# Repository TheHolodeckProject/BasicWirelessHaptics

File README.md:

BasicWirelessHaptics
====================

Simple Unity project to connect to and actuate the Wireless Haptics device

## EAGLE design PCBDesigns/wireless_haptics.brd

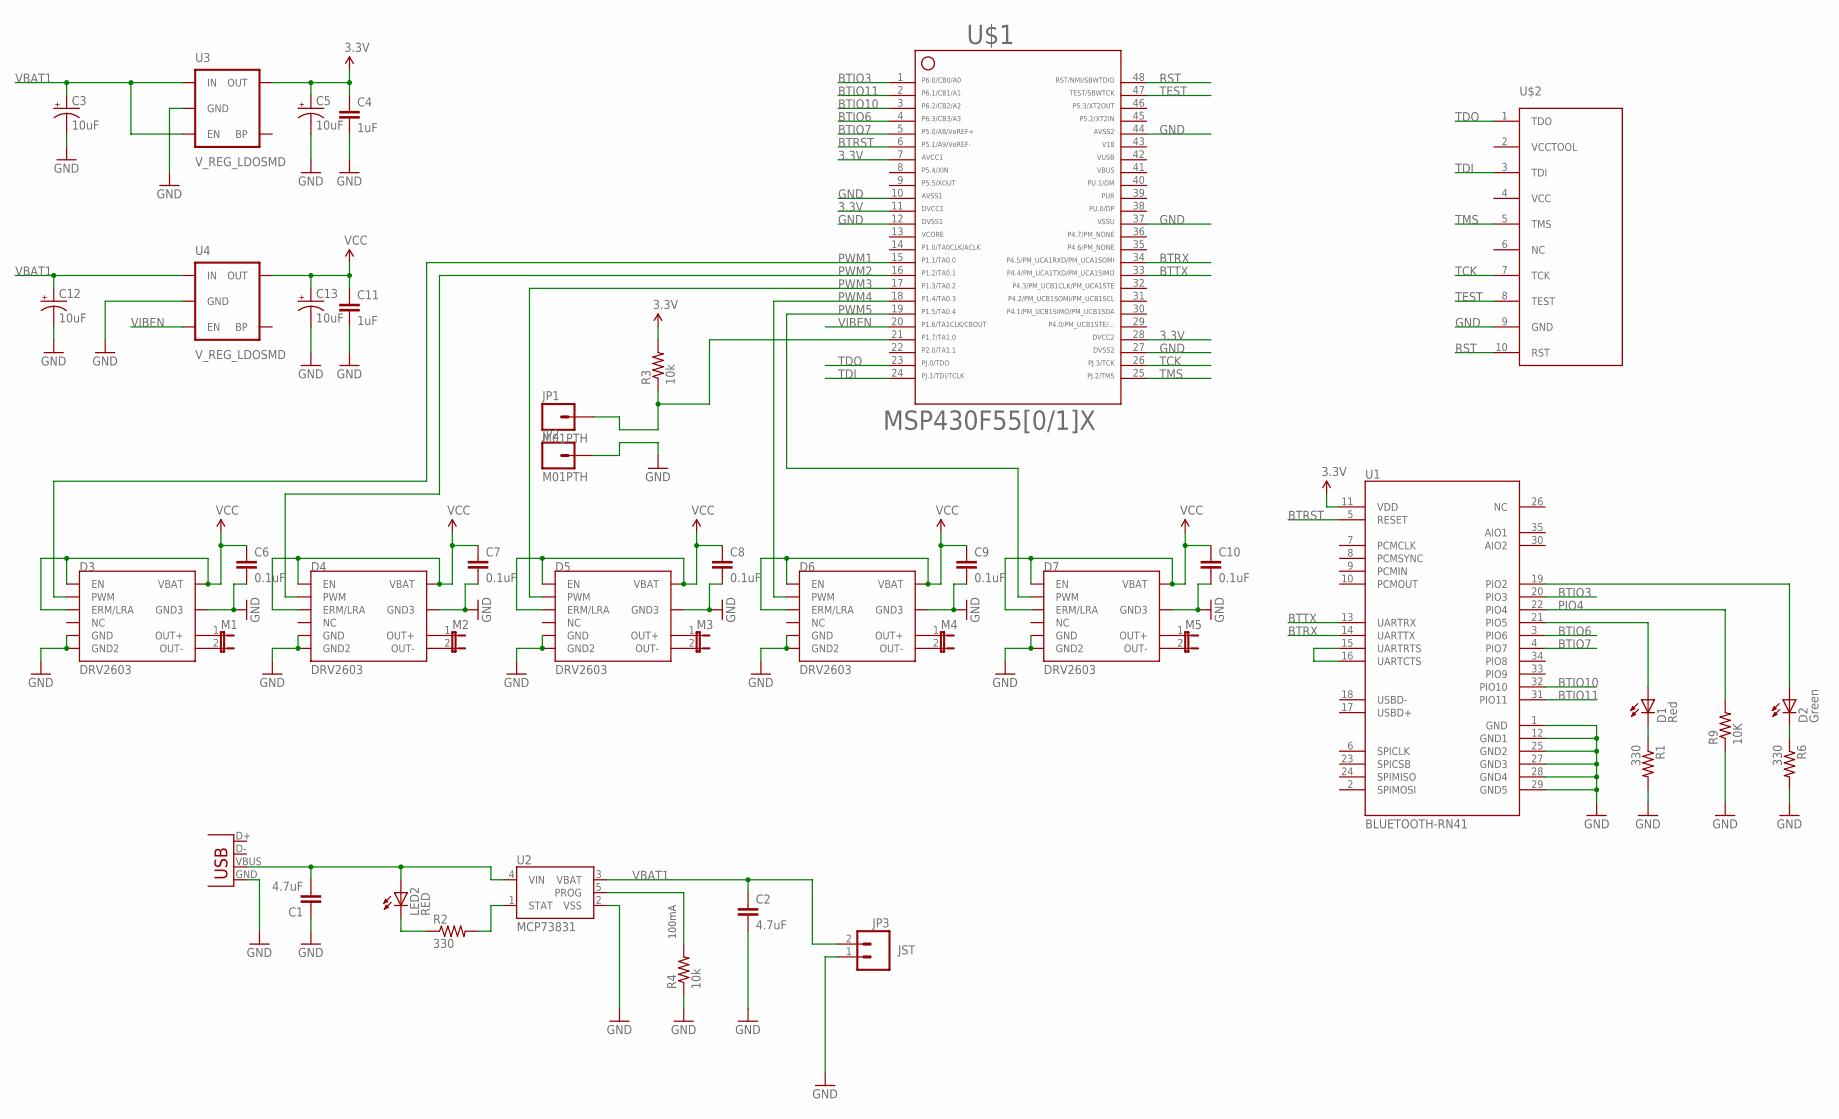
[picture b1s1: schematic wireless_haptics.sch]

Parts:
C1, C2: 4.7uF; 0402-CAP
C3, C5, C12, C13: 10uF; EIA3216
C4, C11: 1uF; 0402-CAP
C6, C7, C8, C9, C10: 0.1uF; 0805
D1: Red; LED-0603
D2: Green; LED-0603
D3, D4, D5, D6, D7: DRV2603; QFN
JP1, JP2: M01PTH; 1X01
JP3: JST; JST-2-PTH
LED2: RED; LED-0603
M1, M2, M3, M4, M5: JUMPER-2PTH; 1X02
R1, R2, R6: 330; 0402-RES
R3, R4: 10k; 0402-RES
R9: 10K; 0402-RES
U1: BLUETOOTH-RN41; RN41
U2: MCP73831; SOT23-5
U3, U4: V_REG_LDOSMD; SOT23-5
U$1: F55[0/1]X---PT48; PT48
U$2: TC2050-NL-MCP-NL; TC2030-MCP-NL
X1: USBSMD; USB-MINIB

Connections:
3.3V: C4.1, C5.A (+), U1.11 (VDD), U3.5 (OUT), U$1.7, U$1.11, U$1.28
13: U$1.13
41: U$1.41
42: U$1.42
43: U$1.43
46: U$1.46
BTIO3: U1.20 (PIO3), U$1.1
BTIO6: U1.3 (PIO6), U$1.4
BTIO7: U1.4 (PIO7), U$1.5
BTIO10: U1.32 (PIO10), U$1.3
BTIO11: U1.31 (PIO11), U$1.2
BTRST: U1.5 (RESET), U$1.6
BTRX: U1.14 (UARTTX), U$1.34
BTTX: U1.13 (UARTRX), U$1.33
D1: D1.C, R1.1
D2: D2.C, R6.1
GND: C1.1, C2.2, C3.C (-), C4.2, C5.C (-), C6.2, C7.2, C8.2, C9.2, C10.2, C11.2, C12.C (-), C13.C (-), D3.P$5 (GND), D3.P$8 (GND2), D3.P$10 (GND3), D4.P$5 (GND), D4.P$8 (GND2), D4.P$10 (GND3), D5.P$5 (GND), D5.P$8 (GND2), D5.P$10 (GND3), D6.P$5 (GND), D6.P$8 (GND2), D6.P$10 (GND3), D7.P$5 (GND), D7.P$8 (GND2), D7.P$10 (GND3), JP2.1, JP3.1, R1.2, R4.1, R6.2, R9.1, U1.1 (GND), U1.12 (GND1), U1.25 (GND2), U1.27 (GND3), U1.28 (GND4), U1.29 (GND5), U2.2 (VSS), U3.2 (GND), U4.2 (GND), U$1.10, U$1.12, U$1.27, U$1.37, U$1.44, U$2.9 (GND), X1.GND
unnamed: D1.A, U1.21 (PIO5)
unnamed: D2.A, U1.19 (PIO2)
unnamed: C1.2, LED2.A, U2.4 (VIN), X1.VBUS
unnamed: D6.P$6 (OUT+), M4.1
unnamed: R2.2, U2.1 (STAT)
unnamed: LED2.C, R2.1
unnamed: D6.P$9 (OUT-), M4.2
unnamed: D7.P$6 (OUT+), M5.1
unnamed: D7.P$9 (OUT-), M5.2
unnamed: D5.P$6 (OUT+), M3.1
unnamed: D5.P$9 (OUT-), M3.2
unnamed: D4.P$6 (OUT+), M2.1
unnamed: D4.P$9 (OUT-), M2.2
unnamed: D3.P$6 (OUT+), M1.1
unnamed: D3.P$9 (OUT-), M1.2
unnamed: U1.15 (UARTRTS), U1.16 (UARTCTS)
unnamed: JP1.1, R3.1, U$1.21
PIO4: R9.2, U1.22 (PIO4)
PROG: R4.2, U2.5 (PROG)
PWM1: D3.P$2 (PWM), U$1.15
PWM2: D4.P$2 (PWM), U$1.16
PWM3: D5.P$2 (PWM), U$1.17
PWM4: D6.P$2 (PWM), U$1.18
PWM5: D7.P$2 (PWM), U$1.19
RST: U$1.48, U$2.10 (RST)
TCK: U$1.26, U$2.7 (TCK)
TDI: U$1.24, U$2.3 (TDI)
TDO: U$1.23, U$2.1 (TDO)
TEST: U$1.47, U$2.8 (TEST)
TMS: U$1.25, U$2.5 (TMS)
VBAT1: C2.1, C3.A (+), C12.A (+), JP3.2, U2.3 (VBAT), U3.1 (IN), U3.3 (EN), U4.1 (IN)
VCC: C6.1, C7.1, C8.1, C9.1, C10.1, C11.1, C13.A (+), D3.P$1 (EN), D3.P$3 (ERM/LRA), D3.P$7 (VBAT), D4.P$1 (EN), D4.P$3 (ERM/LRA), D4.P$7 (VBAT), D5.P$1 (EN), D5.P$3 (ERM/LRA), D5.P$7 (VBAT), D6.P$1 (EN), D6.P$3 (ERM/LRA), D6.P$7 (VBAT), D7.P$1 (EN), D7.P$3 (ERM/LRA), D7.P$7 (VBAT), R3.2, U4.5 (OUT)
VIBEN: U4.3 (EN), U$1.20

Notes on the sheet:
100mA

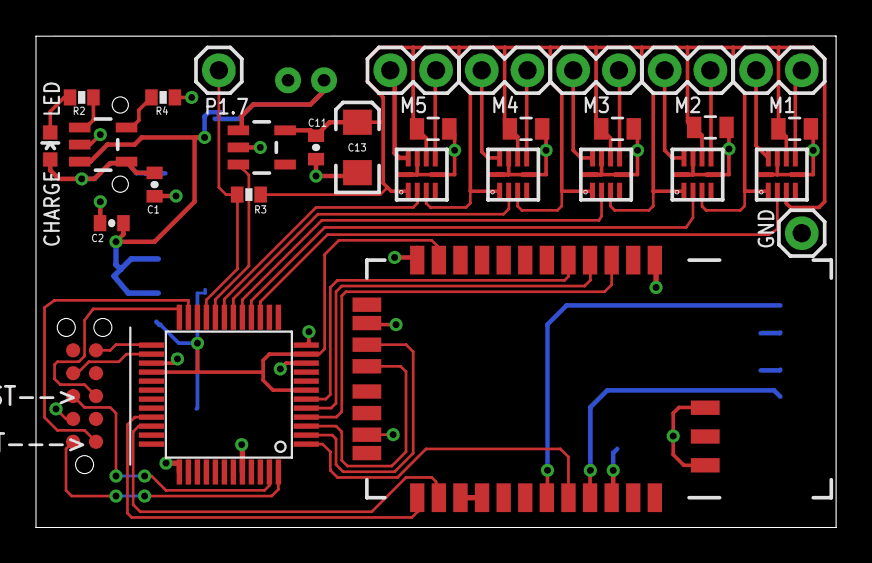
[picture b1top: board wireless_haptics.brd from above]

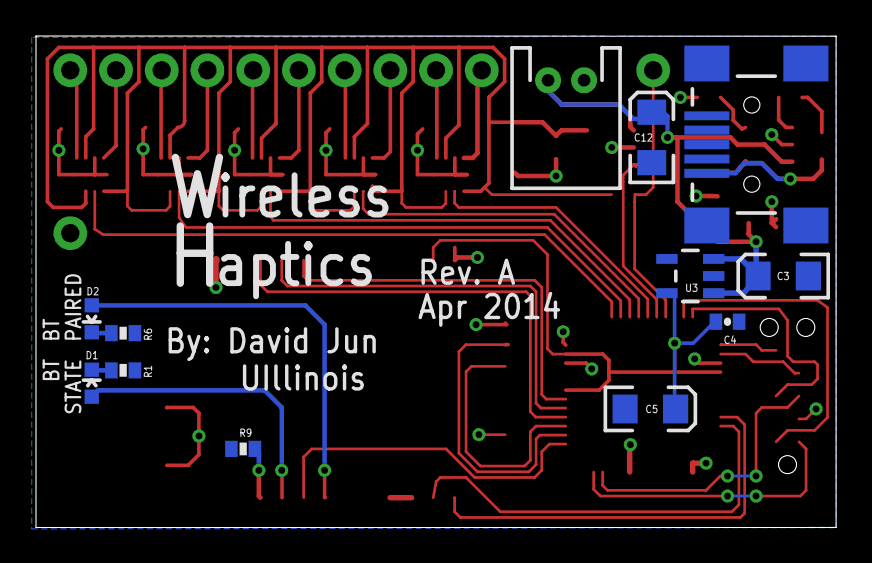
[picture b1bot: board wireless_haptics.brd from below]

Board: 2 copper layers, 44.5 x 27.3 mm, 42 parts (12 on the bottom side), 45 nets.

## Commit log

2014-06-06 basic Unity app with GUI to connect to bluetooth SPP.
2014-08-25 moved unity project to a subfolder
2014-08-25 firmware for msp430f5510 on wireless haptic board.
2014-10-01 Added Code Composer workspace
2014-10-01 Updated HapticsGlove to most up to date version from Andres computer
2014-10-01 Updated to now have latest version of BasicUnityProject from Andres computer

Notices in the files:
parts and their libraries:
TC2050: ©2009 ROFA.cz
SparkFun-Connectors: Licensing: Creative Commons ShareAlike 4.0 International - https://creativecommons.org/licenses/by-sa/4.0
SparkFun-Aesthetics: Licensing: CC v3.0 Share-Alike You are welcome to use this library for commercial purposes.
